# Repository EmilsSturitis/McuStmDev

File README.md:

# McuStmDev
simple stm32 dev pcb

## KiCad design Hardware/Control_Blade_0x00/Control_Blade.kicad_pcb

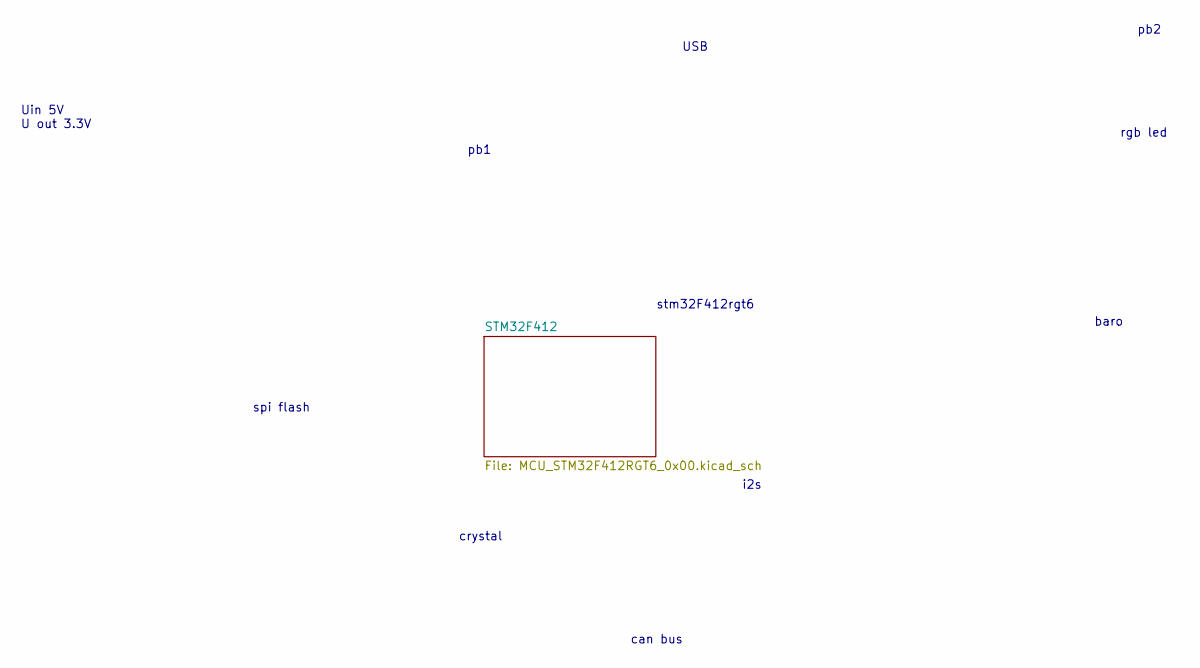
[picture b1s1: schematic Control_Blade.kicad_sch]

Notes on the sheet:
spi flash
Uin 5V U out 3.3V
pb2
baro
stm32F412rgt6
i2s
can bus
crystal
USB
rgb led
pb1

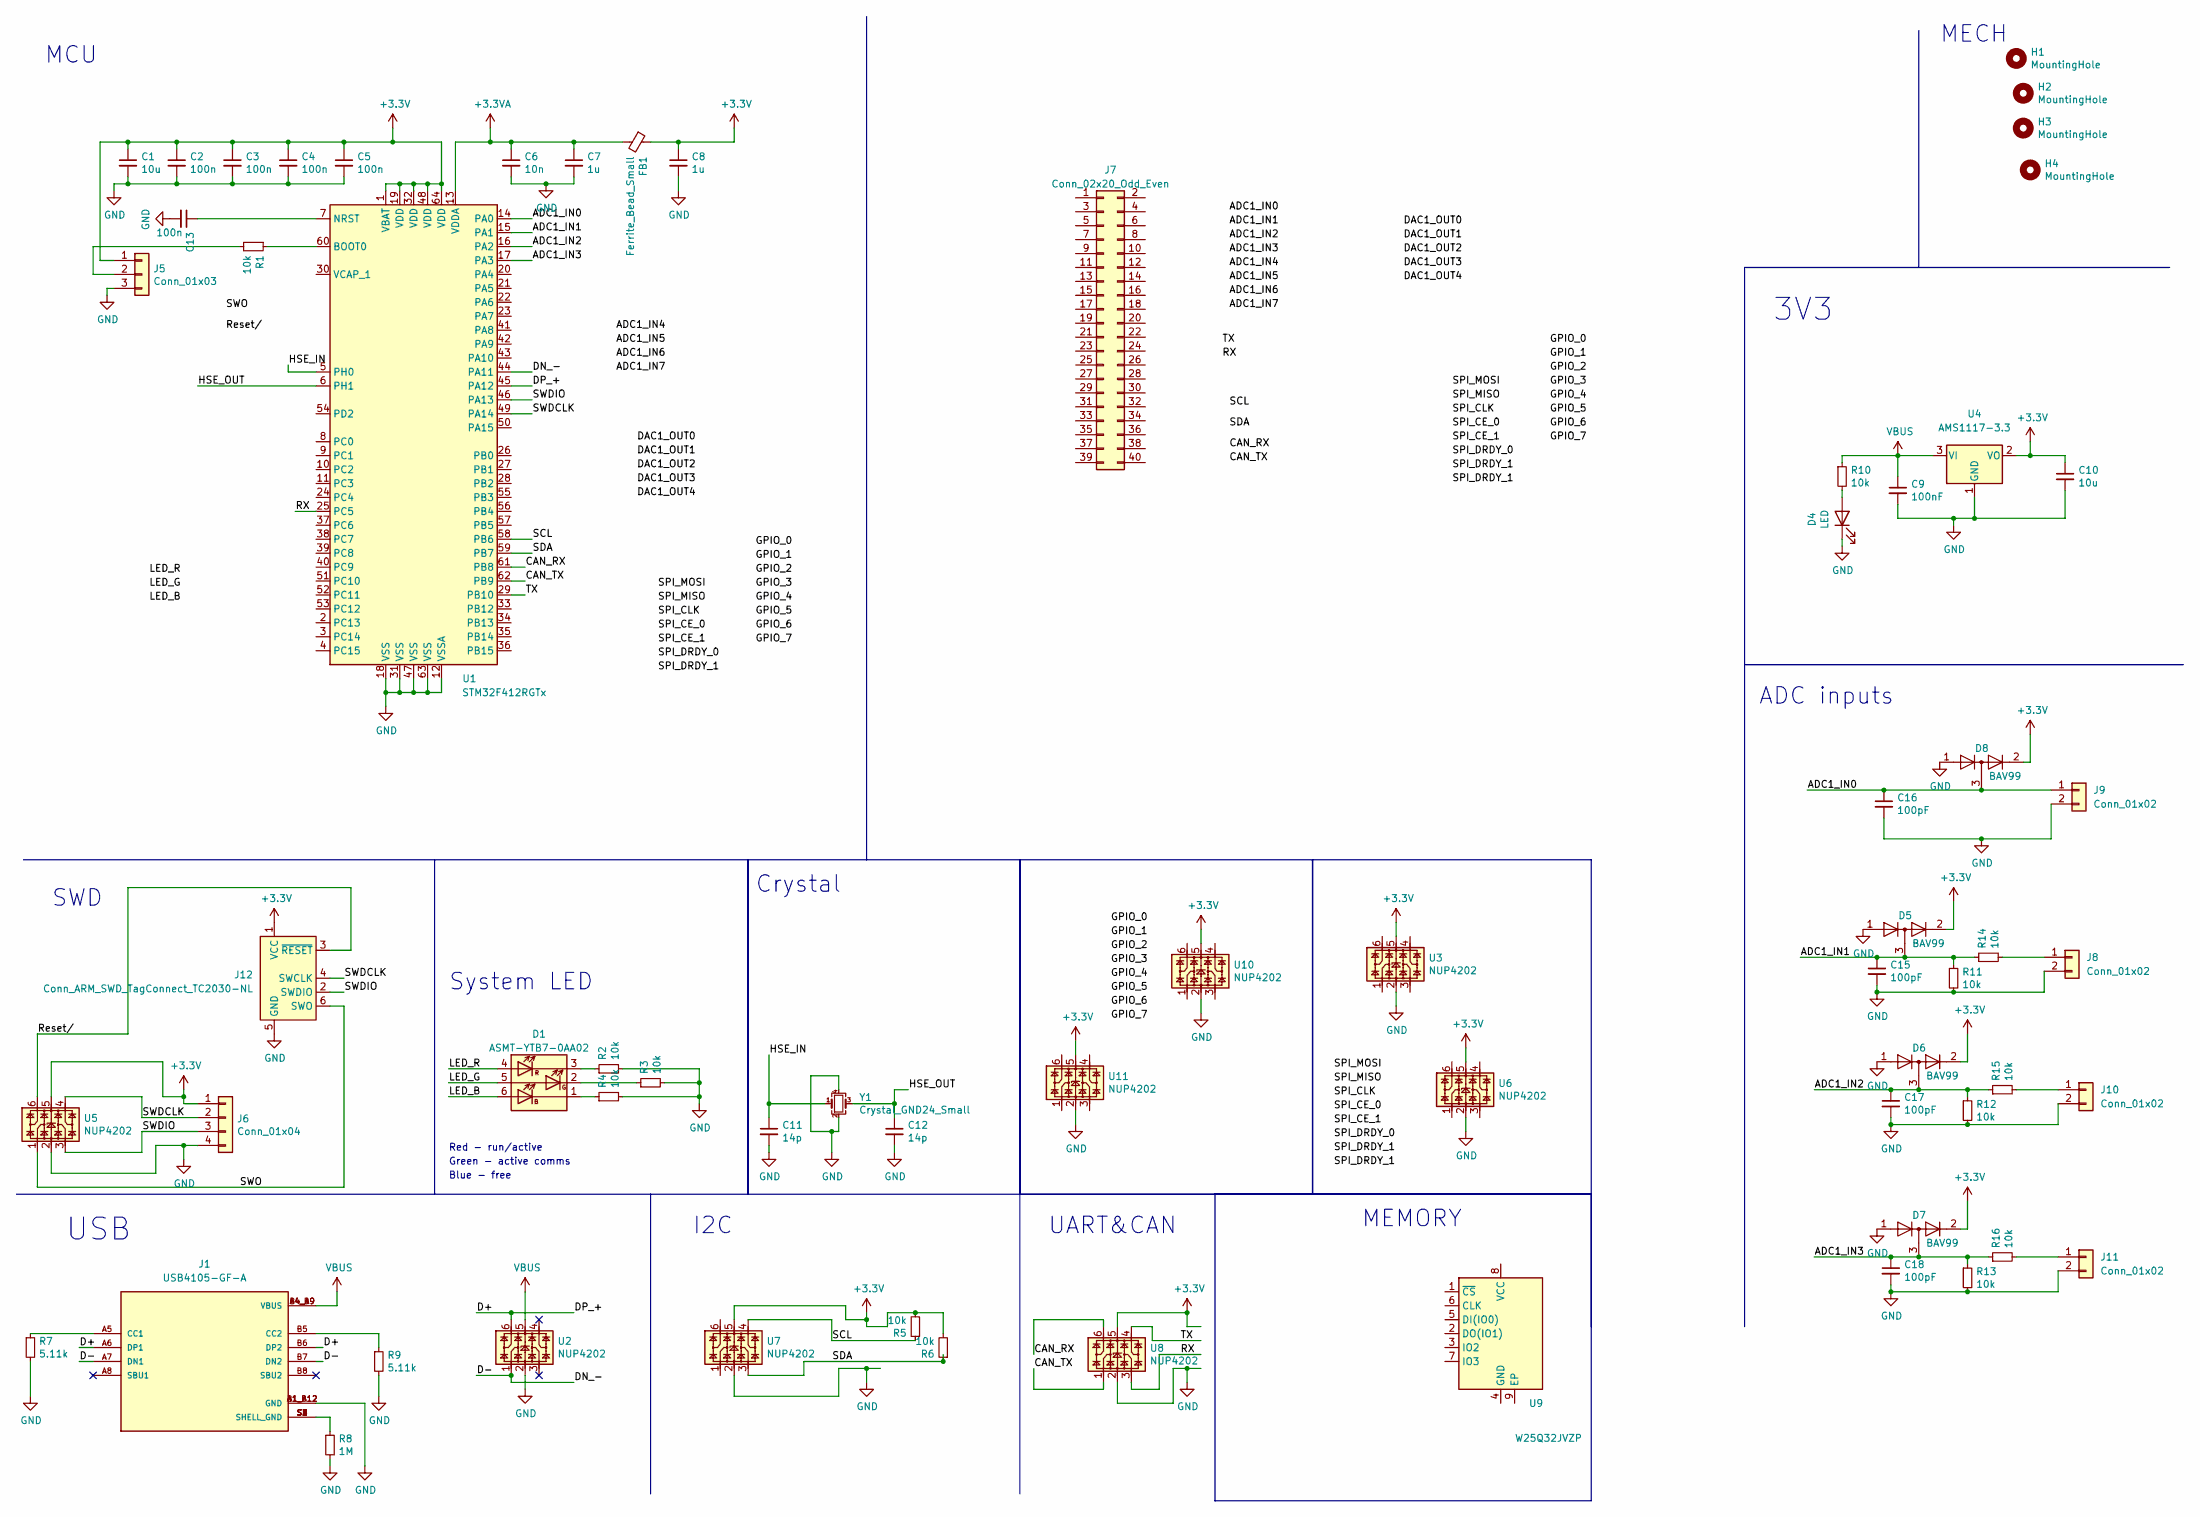
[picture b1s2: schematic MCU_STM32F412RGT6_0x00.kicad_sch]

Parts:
C1, C10: 10u; C_0805_2012Metric_Pad1.18x1.45mm_HandSolder
C2, C3, C4, C5, C13: 100n; C_0805_2012Metric_Pad1.18x1.45mm_HandSolder
C6: 10n; C_0805_2012Metric_Pad1.18x1.45mm_HandSolder
C7, C8: 1u; C_0805_2012Metric_Pad1.18x1.45mm_HandSolder
C9: 100nF; C_0805_2012Metric_Pad1.18x1.45mm_HandSolder
C11, C12: 14p; C_0805_2012Metric_Pad1.18x1.45mm_HandSolder
C15, C16, C17, C18: 100pF; C_0805_2012Metric_Pad1.18x1.45mm_HandSolder
D1: ASMT-YTB7-0AA02; LED_Avago_PLCC6_3x2.8mm
D4: LED; LED_PLCC-2
D5, D6, D7, D8: BAV99; SOT-23
FB1: Ferrite_Bead_Small; L_0805_2012Metric_Pad1.15x1.40mm_HandSolder
H1, H2, H3, H4: MountingHole; MountingHole_3.2mm_M3_DIN965
J1: USB4105-GF-A; GCT_USB4105-GF-A; PARTREV A3
J5: Conn_01x03; PinSocket_1x03_P2.54mm_Vertical
J6: Conn_01x04; JST_XH_S4B-XH-A_1x04_P2.50mm_Horizontal
J7: Conn_02x20_Odd_Even; PinSocket_2x20_P2.54mm_Horizontal
J8, J9, J10, J11: Conn_01x02; PinHeader_1x02_P2.54mm_Horizontal
J12: Conn_ARM_SWD_TagConnect_TC2030-NL; Tag-Connect_TC2030-IDC-NL_2x03_P1.27mm_Vertical
R1, R10, R11, R12, R13, R14, R15, R16: 10k; R_0805_2012Metric_Pad1.20x1.40mm_HandSolder
R2, R3, R4: 10k; R_0603_1608Metric
R5, R6: 10k; R_0805_2012Metric
R7, R9: 5.11k; R_0805_2012Metric_Pad1.20x1.40mm_HandSolder
R8: 1M; R_0805_2012Metric_Pad1.20x1.40mm_HandSolder
U1: STM32F412RGTx; LQFP-64_10x10mm_P0.5mm
U2, U3, U5, U6, U7, U8, U10, U11: NUP4202; SOT-363_SC-70-6
U4: AMS1117-3.3; SOT-223-3_TabPin2
U9: W25Q32JVZP; WSON-8-1EP_6x5mm_P1.27mm_EP3.4x4.3mm
Y1: Crystal_GND24_Small; Crystal_SMD_Abracon_ABM10-4Pin_2.5x2.0mm; MPN ABM10-16.000MHZ-R80-7-D30-T

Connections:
+3.3VA: C6.1, C7.1, FB1.2, U1.13 (VDDA)
+3V3: C1.1, C2.1, C3.1, C4.1, C5.1, C8.1, C10.1, D5.2 (A), D6.2 (A), D7.2 (A), D8.2 (A), FB1.1, J5.1, J6.1, J12.1 (VCC), R5.2, R6.2, U1.1 (VBAT), U1.19 (VDD), U1.32 (VDD), U1.48 (VDD), U1.64 (VDD), U3.5, U4.2 (VO), U5.5, U6.5, U7.5, U8.5, U9.5 (DI(IO0)), U10.5, U11.5
/STM32F412/ADC1_IN0: C16.1, D8.3 (K), J9.1, U1.14 (PA0)
/STM32F412/ADC1_IN1: C15.1, D5.3 (K), R11.1, R14.1, U1.15 (PA1)
/STM32F412/ADC1_IN2: C17.1, D6.3 (K), R12.1, R15.1, U1.16 (PA2)
/STM32F412/ADC1_IN3: C18.1, D7.3 (K), R13.1, R16.1, U1.17 (PA3)
/STM32F412/CAN_RX: U1.61 (PB8), U8.6, U9.4 (GND)
/STM32F412/CAN_TX: U1.62 (PB9), U8.1, U9.3 (IO2)
/STM32F412/D+: J1.A6 (DP1), J1.B6 (DP2), U1.45 (PA12), U2.6
/STM32F412/D-: J1.A7 (DN1), J1.B7 (DN2), U1.44 (PA11), U2.1
/STM32F412/HSE_IN: C11.1, U1.5 (PH0), Y1.1
/STM32F412/HSE_OUT: C12.1, U1.6 (PH1), Y1.3
/STM32F412/LED_B: D1.6 (AB)
/STM32F412/LED_G: D1.5 (AG)
/STM32F412/LED_R: D1.4 (AR)
/STM32F412/RX: U1.25 (PC5), U8.3
/STM32F412/Reset/: J12.3 (~RESET), U5.6
/STM32F412/SCL: R5.1, U1.58 (PB6), U7.4
/STM32F412/SDA: R6.1, U1.59 (PB7), U7.3
/STM32F412/SWDCLK: J6.2, J12.4 (SWCLK), U1.49 (PA14), U5.4
/STM32F412/SWDIO: J6.3, J12.2 (SWDIO), U1.46 (PA13), U5.3
/STM32F412/SWO: J12.6 (SWO), U5.1
/STM32F412/TX: U1.29 (PB10), U8.4
GND: C1.2, C2.2, C3.2, C4.2, C5.2, C6.2, C7.2, C8.2, C9.2, C10.2, C11.2, C12.2, C13.2, C15.2, C16.2, C17.2, C18.2, D4.1 (K), D5.1 (K), D6.1 (K), D7.1 (K), D8.1 (K), J1.A1_B12 (GND), J1.B1_A12 (GND), J5.3, J6.4, J8.2, J9.2, J10.2, J11.2, J12.5 (GND), R2.2, R3.2, R4.2, R7.2, R8.2, R9.2, R11.2, R12.2, R13.2, U1.12 (VSSA), U1.18 (VSS), U1.31 (VSS), U1.47 (VSS), U1.63 (VSS), U2.2, U3.2, U4.1 (GND), U5.2, U6.2, U7.2, U8.2, U9.2 (DO(IO1)), U10.2, U11.2, Y1.2, Y1.4
unnamed: D1.1 (KB), R4.1
unnamed: D1.2 (KG), R3.1
unnamed: D1.3 (KR), R2.1
unnamed: D4.2 (A), R10.2
unnamed: J1.A5 (CC1), R7.1
unnamed: J1.B5 (CC2), R9.1
unnamed: J1.S1 (SHELL_GND), J1.S2 (SHELL_GND), J1.S3 (SHELL_GND), J1.S4 (SHELL_GND), R8.1
unnamed: J5.2, R1.2
unnamed: J8.1, R14.2
unnamed: J10.1, R15.2
unnamed: J11.1, R16.2
unnamed: R1.1, U1.60 (BOOT0)
unnamed: C13.1, U1.7 (NRST)
VBUS: C9.1, J1.A4_B9 (VBUS), J1.B4_A9 (VBUS), R10.1, U2.5, U4.3 (VI)

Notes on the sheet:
Red - run/active
MECH
MCU
I2C
SWD
MEMORY
Crystal
USB
Blue - free
UART&CAN
Green - active comms
3V3
System LED
ADC inputs

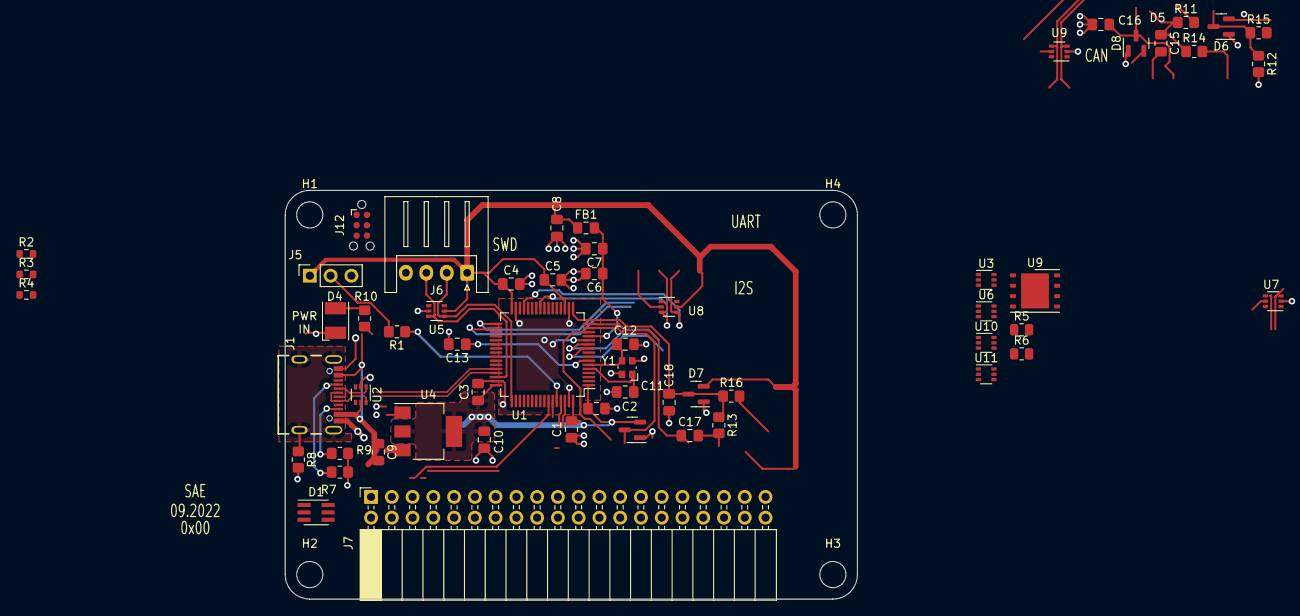
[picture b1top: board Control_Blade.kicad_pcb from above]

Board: 4 copper layers, 70.0 x 50.0 mm, 62 parts (0 on the bottom side), 32 nets.

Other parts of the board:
U9#2: W25Q32JVZP; WSON-8-1EP_6x5mm_P1.27mm_EP3.4x4.3mm

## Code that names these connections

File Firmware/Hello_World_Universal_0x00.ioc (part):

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Mcu.Name=STM32F412R(E-G)Tx
Mcu.Package=LQFP64
Mcu.UserName=STM32F412RGTx
PA0.Signal=ADCx_IN0
PA1.Signal=ADCx_IN1
PA11.Mode=Device_Only
PA11.Signal=USB_OTG_FS_DM
PA12.Mode=Device_Only
PA12.Signal=USB_OTG_FS_DP
PA13.Mode=Serial_Wire
PA13.Signal=SYS_JTMS-SWDIO
PA14.Mode=Serial_Wire
PA14.Signal=SYS_JTCK-SWCLK
PA2.Signal=ADCx_IN2
PA3.Signal=ADCx_IN3
PB10.Mode=Asynchronous
PB10.Signal=USART3_TX
PB12.GPIOParameters=GPIO_Label
PB12.GPIO_Label=LED_1
PB12.Signal=GPIO_Output
PB13.GPIOParameters=GPIO_Label
PB13.GPIO_Label=LED_2
PB13.Signal=GPIO_Output
PB6.Mode=I2C
PB6.Signal=I2C1_SCL
PB7.Mode=I2C
PB7.Signal=I2C1_SDA
PB8.Mode=CAN_Activate
PB8.Signal=CAN1_RX
PB9.Mode=CAN_Activate
PB9.Signal=CAN1_TX
PC2.GPIOParameters=GPIO_Label
PC2.GPIO_Label=LED_3
PC2.Signal=GPIO_Output
PC3.GPIOParameters=GPIO_Label
PC3.GPIO_Label=LED_4
PC3.Signal=GPIO_Output
PC5.Mode=Asynchronous
PC5.Signal=USART3_RX
PH0\ -\ OSC_IN.Mode=HSE-External-Oscillator
PH0\ -\ OSC_IN.Signal=RCC_OSC_IN
PH1\ -\ OSC_OUT.Mode=HSE-External-Oscillator
PH1\ -\ OSC_OUT.Signal=RCC_OSC_OUT
RCC.HSE_VALUE=16000000
board=custom

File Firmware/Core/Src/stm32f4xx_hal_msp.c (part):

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
    __HAL_RCC_GPIOA_CLK_ENABLE();
    /**ADC1 GPIO Configuration
    PA0     ------> ADC1_IN0
    PA1     ------> ADC1_IN1
    PA2     ------> ADC1_IN2
    PA3     ------> ADC1_IN3
    */
    GPIO_InitStruct.Pin = GPIO_PIN_0|GPIO_PIN_1|GPIO_PIN_2|GPIO_PIN_3;
    GPIO_InitStruct.Mode = GPIO_MODE_ANALOG;
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    __HAL_RCC_ADC1_CLK_DISABLE();

    /**ADC1 GPIO Configuration
    PA0     ------> ADC1_IN0
    PA1     ------> ADC1_IN1
    PA2     ------> ADC1_IN2
    PA3     ------> ADC1_IN3
    */
    HAL_GPIO_DeInit(GPIOA, GPIO_PIN_0|GPIO_PIN_1|GPIO_PIN_2|GPIO_PIN_3);

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
    __HAL_RCC_GPIOB_CLK_ENABLE();
    /**CAN1 GPIO Configuration
    PB8     ------> CAN1_RX
    PB9     ------> CAN1_TX
    */
    GPIO_InitStruct.Pin = GPIO_PIN_8|GPIO_PIN_9;
    GPIO_InitStruct.Mode = GPIO_MODE_AF_PP;
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    __HAL_RCC_CAN1_CLK_DISABLE();

    /**CAN1 GPIO Configuration
    PB8     ------> CAN1_RX
    PB9     ------> CAN1_TX
    */
    HAL_GPIO_DeInit(GPIOB, GPIO_PIN_8|GPIO_PIN_9);

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
    __HAL_RCC_GPIOB_CLK_ENABLE();
    /**I2C1 GPIO Configuration
    PB6     ------> I2C1_SCL
    PB7     ------> I2C1_SDA
    */
    GPIO_InitStruct.Pin = GPIO_PIN_6|GPIO_PIN_7;
    GPIO_InitStruct.Mode = GPIO_MODE_AF_OD;
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    __HAL_RCC_I2C1_CLK_DISABLE();

    /**I2C1 GPIO Configuration
    PB6     ------> I2C1_SCL
    PB7     ------> I2C1_SDA
    */
    HAL_GPIO_DeInit(GPIOB, GPIO_PIN_6);

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    __HAL_RCC_GPIOC_CLK_ENABLE();
    __HAL_RCC_GPIOB_CLK_ENABLE();
    /**USART3 GPIO Configuration
    PC5     ------> USART3_RX
    PB10     ------> USART3_TX
    */
    GPIO_InitStruct.Pin = GPIO_PIN_5;
    GPIO_InitStruct.Mode = GPIO_MODE_AF_PP;
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    __HAL_RCC_USART3_CLK_DISABLE();

    /**USART3 GPIO Configuration
    PC5     ------> USART3_RX
    PB10     ------> USART3_TX
    */
    HAL_GPIO_DeInit(GPIOC, GPIO_PIN_5);

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
    __HAL_RCC_GPIOA_CLK_ENABLE();
    /**USB_OTG_FS GPIO Configuration
    PA11     ------> USB_OTG_FS_DM
    PA12     ------> USB_OTG_FS_DP
    */
    GPIO_InitStruct.Pin = GPIO_PIN_11|GPIO_PIN_12;
    GPIO_InitStruct.Mode = GPIO_MODE_AF_PP;
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    __HAL_RCC_USB_OTG_FS_CLK_DISABLE();

    /**USB_OTG_FS GPIO Configuration
    PA11     ------> USB_OTG_FS_DM
    PA12     ------> USB_OTG_FS_DP
    */
    HAL_GPIO_DeInit(GPIOA, GPIO_PIN_11|GPIO_PIN_12);

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
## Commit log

2022-07-26 innitial commit
2022-09-19 new usb connector and pcb size defined
2022-09-20 Final layout for V1, sent of to FAB
2023-03-04 added STM32CubeIDE project for Universal 0x00
2023-03-05 added Control_Blade from universal project

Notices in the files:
Firmware/Core/Src/stm32f4xx_hal_msp.c:
Copyright (c) 2023 STMicroelectronics.
All rights reserved.
This software is licensed under terms that can be found in the LICENSE file
